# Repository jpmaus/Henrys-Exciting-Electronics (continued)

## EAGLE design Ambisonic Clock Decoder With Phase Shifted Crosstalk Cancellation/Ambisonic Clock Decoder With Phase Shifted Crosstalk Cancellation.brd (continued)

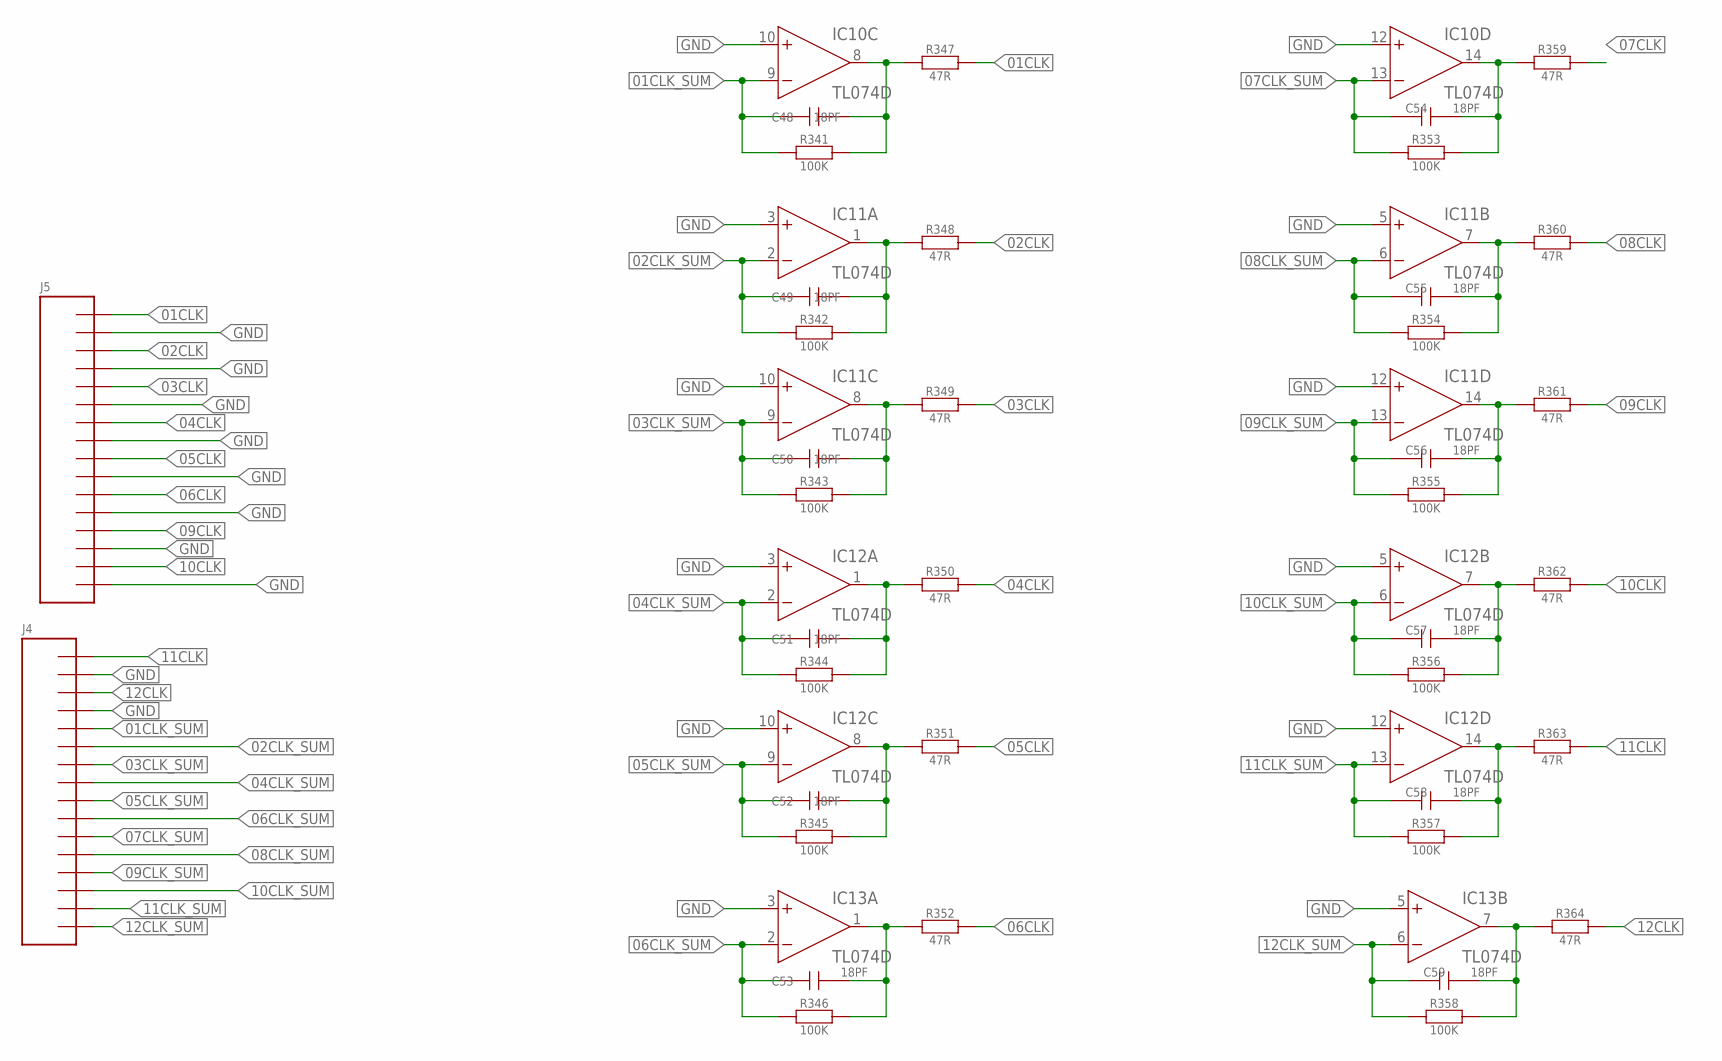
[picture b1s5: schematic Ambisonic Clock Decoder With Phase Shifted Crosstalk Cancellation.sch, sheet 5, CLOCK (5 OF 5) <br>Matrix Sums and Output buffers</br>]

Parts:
C48, C49, C50, C51, C52, C53, C54, C55, C56, C57, C58, C59: 18PF; CT6032
IC10, IC11, IC12, IC13: TL074D; SO14
J4, J5: CON_16; 2X08SMT
R341, R342, R343, R344, R345, R346, R353, R354, R355, R356, R357, R358: 100K; R6332W
R347, R348, R349, R350, R351, R352, R359, R360, R361, R362, R363, R364: 47R; R6332W

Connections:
01CLK: J5.1, R347.2
01CLK_SUM: C48.+ (1), IC10.9 (-IN), J4.5, R341.1
02CLK: J5.3, R348.2
02CLK_SUM: C49.+ (1), IC11.2 (-IN), J4.6, R342.1
03CLK: J5.5, R349.2
03CLK_SUM: C50.+ (1), IC11.9 (-IN), J4.7, R343.1
04CLK: J5.7, R350.2
04CLK_SUM: C51.+ (1), IC12.2 (-IN), J4.8, R344.1
05CLK: J5.9, R351.2
05CLK_SUM: C52.+ (1), IC12.9 (-IN), J4.9, R345.1
06CLK: J5.11, R352.2
06CLK_SUM: C53.+ (1), IC13.2 (-IN), J4.10, R346.1
07CLK: R359.2
07CLK_SUM: C54.+ (1), IC10.13 (-IN), J4.11, R353.1
08CLK: R360.2
08CLK_SUM: C55.+ (1), IC11.6 (-IN), J4.12, R354.1
09CLK: J5.13, R361.2
09CLK_SUM: C56.+ (1), IC11.13 (-IN), J4.13, R355.1
10CLK: J5.15, R362.2
10CLK_SUM: C57.+ (1), IC12.6 (-IN), J4.14, R356.1
11CLK: J4.1, R363.2
11CLK_SUM: C58.+ (1), IC12.13 (-IN), J4.15, R357.1
12CLK: J4.3, R364.2
12CLK_SUM: C59.+ (1), IC13.6 (-IN), J4.16, R358.1
GND: IC10.10 (+IN), IC10.12 (+IN), IC11.3 (+IN), IC11.5 (+IN), IC11.10 (+IN), IC11.12 (+IN), IC12.3 (+IN), IC12.5 (+IN), IC12.10 (+IN), IC12.12 (+IN), IC13.3 (+IN), IC13.5 (+IN), J4.2, J4.4, J5.2, J5.4, J5.6, J5.8, J5.10, J5.12, J5.14, J5.16; also elsewhere on the board
unnamed: C48.- (2), IC10.8 (OUT), R341.2, R347.1
unnamed: C49.- (2), IC11.1 (OUT), R342.2, R348.1
unnamed: C50.- (2), IC11.8 (OUT), R343.2, R349.1
unnamed: C51.- (2), IC12.1 (OUT), R344.2, R350.1
unnamed: C52.- (2), IC12.8 (OUT), R345.2, R351.1
unnamed: C53.- (2), IC13.1 (OUT), R346.2, R352.1
unnamed: C54.- (2), IC10.14 (OUT), R353.2, R359.1
unnamed: C55.- (2), IC11.7 (OUT), R354.2, R360.1
unnamed: C56.- (2), IC11.14 (OUT), R355.2, R361.1
unnamed: C57.- (2), IC12.7 (OUT), R356.2, R362.1
unnamed: C58.- (2), IC12.14 (OUT), R357.2, R363.1
unnamed: C59.- (2), IC13.7 (OUT), R358.2, R364.1
V+: IC10.4 (V+), IC11.4 (V+), IC12.4 (V+), IC13.4 (V+); also elsewhere on the board
V-: IC10.11 (V-), IC11.11 (V-), IC12.11 (V-), IC13.11 (V-); also elsewhere on the board

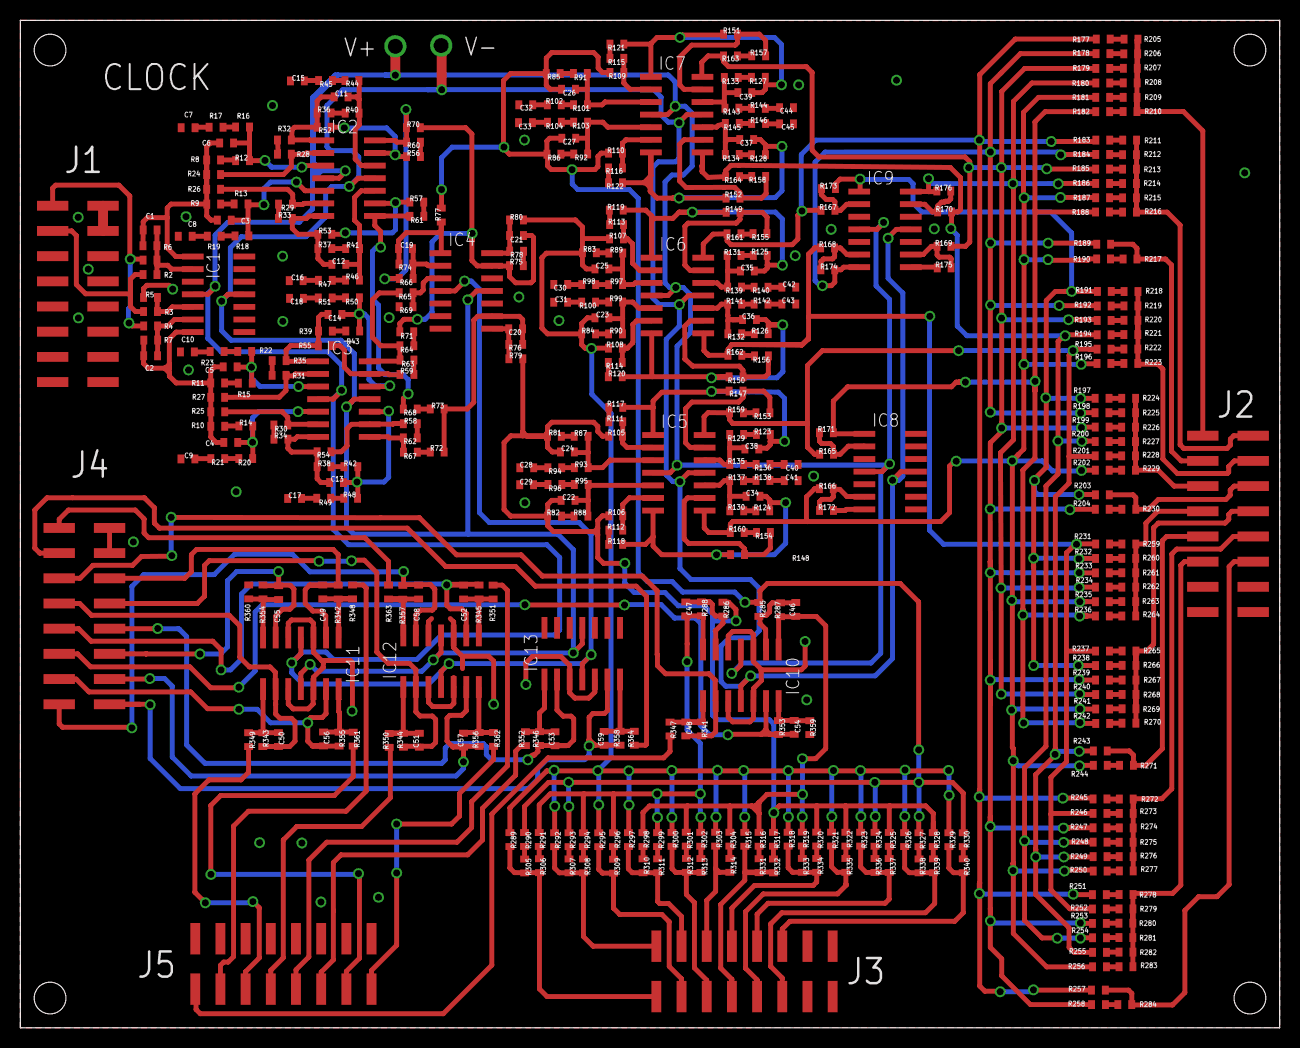
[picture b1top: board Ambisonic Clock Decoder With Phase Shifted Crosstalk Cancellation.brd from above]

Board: 2 copper layers, 127.0 x 101.6 mm, 441 parts (0 on the bottom side), 310 nets.

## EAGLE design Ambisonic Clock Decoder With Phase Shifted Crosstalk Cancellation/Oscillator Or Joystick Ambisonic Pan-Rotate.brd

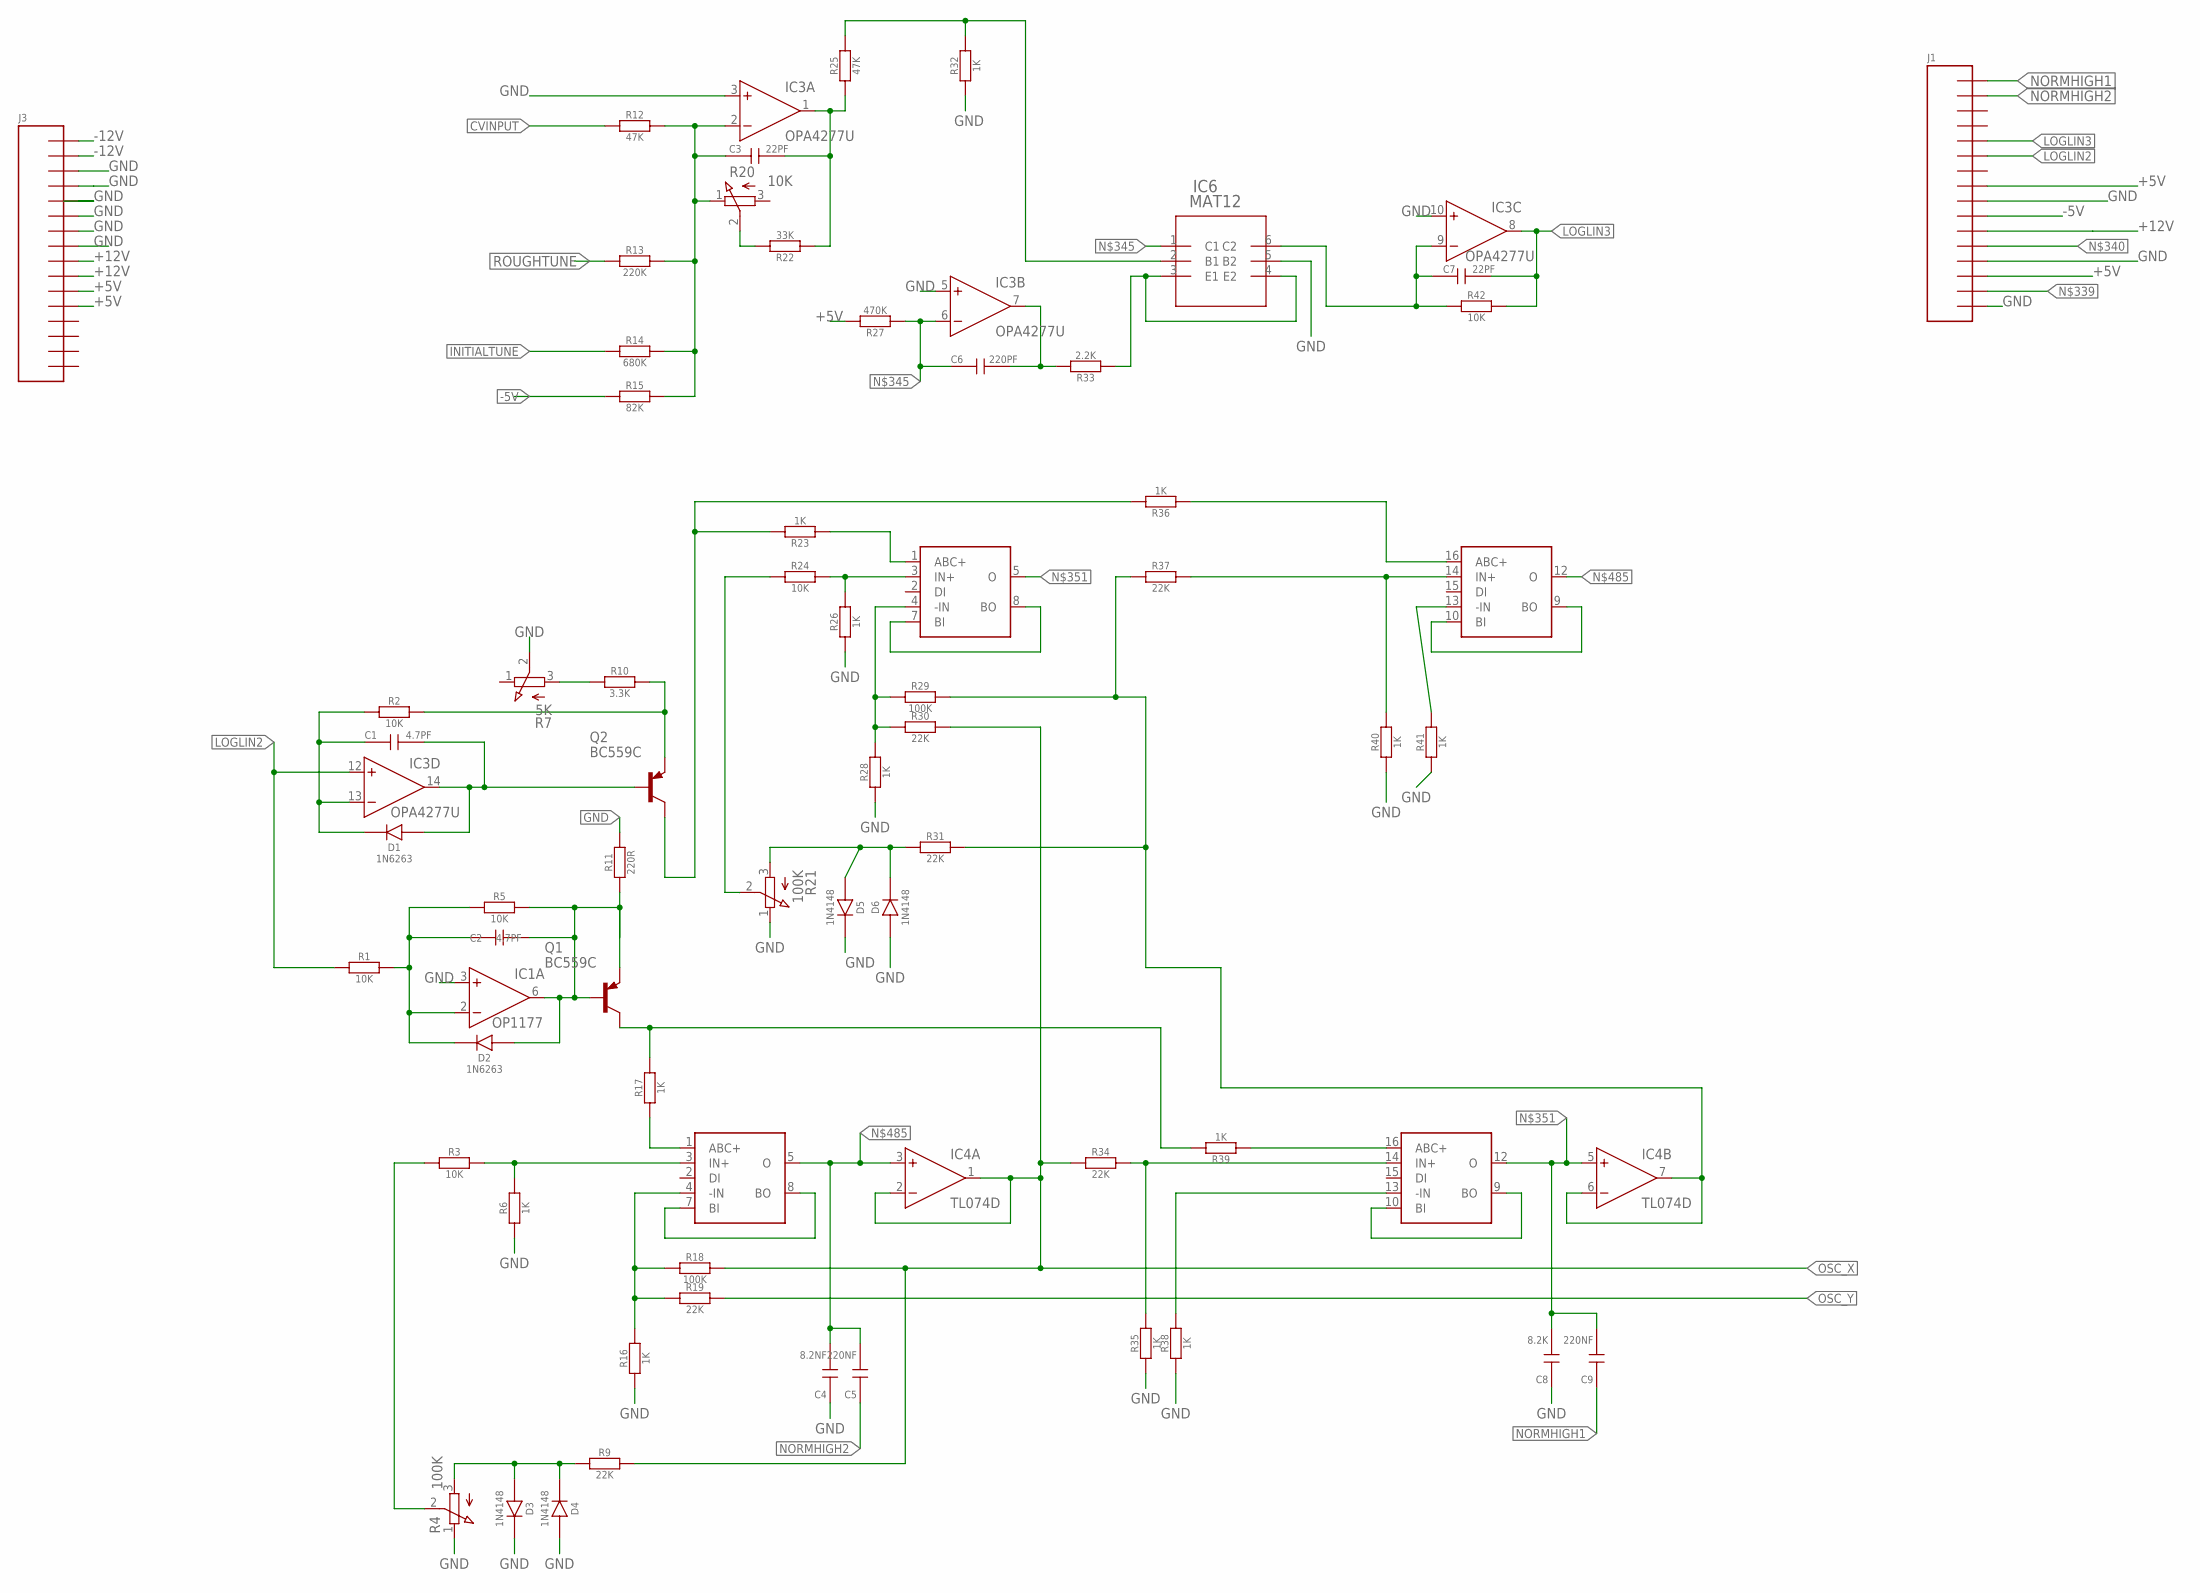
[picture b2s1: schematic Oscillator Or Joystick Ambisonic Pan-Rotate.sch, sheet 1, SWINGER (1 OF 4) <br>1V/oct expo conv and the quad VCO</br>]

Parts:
C1, C2: 4.7PF; CT6032
C3, C7: 22PF; CT6032
C4: 8.2NF; CT6032
C5, C9: 220NF; CT6032
C6: 220PF; CT6032
C8: 8.2K; CT6032
D1, D2: 1N6263; SOD123
D3, D4, D5, D6: 1N4148; SOD123
IC1: OP1177; SO08
IC2, IC5: LM13700; SO16
IC3: OPA4277U; SO14
IC4: TL074D; SO14
IC6: MAT12; H_6
J1, J3: CON_16; 2X08SMT
Q1, Q2: BC559C; TO92
R1, R2, R3, R5, R24, R42: 10K; R6332W
R4, R21: 100K; TRIM
R6, R16, R17, R23, R26, R28, R32, R35, R36, R38, R39, R40, R41: 1K; R6332W
R7: 5K; TRIM
R9, R19, R30, R31, R34, R37: 22K; R6332W
R10: 3.3K; R6332W
R11: 220R; R6332W
R12, R25: 47K; R6332W
R13: 220K; R6332W
R14: 680K; R6332W
R15: 82K; R6332W
R18, R29: 100K; R6332W
R20: 10K; TRIM
R22: 33K; R6332W
R27: 470K; R6332W
R33: 2.2K; R6332W

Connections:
+5V: J1.8, J1.14, J3.11, J3.12, R27.2; also elsewhere on the board
+12V: IC2.11 (V+), IC4.4 (V+), J1.11, J3.9, J3.10; also elsewhere on the board
-5V: J1.10, R15.1; also elsewhere on the board
-12V: IC2.6 (V-), IC4.11 (V-), J3.1, J3.2; also elsewhere on the board
CVINPUT: R12.1
GND: C4.+ (1), C8.+ (1), D3.C, D4.A, D5.C, D6.A, IC1.3 (+IN), IC3.3 (+IN), IC3.5 (+IN), IC3.10 (+IN), IC6.5 (B2), J1.9, J1.13, J1.16, J3.3, J3.4, J3.5, J3.6, J3.7, J3.8, R4.1 (A), R6.1, R7.2 (E), R11.2, R16.1, R21.1 (A), R26.1, R28.1, R32.1, R35.1, R38.1, R40.1, R41.1; also elsewhere on the board
INITIALTUNE: R14.1
LOGLIN2: IC3.12 (+IN), J1.6, R1.1
LOGLIN3: C7.- (2), IC3.8 (OUT), J1.5, R42.2
unnamed: C3.+ (1), IC3.2 (-IN), R12.2, R13.2, R14.2, R15.2, R20.1 (A)
unnamed: C3.- (2), IC3.1 (OUT), R22.1, R25.1
unnamed: IC6.2 (B1), R25.2, R32.2
unnamed: C6.- (2), IC3.7 (OUT), R33.2
unnamed: IC6.3 (E1), IC6.4 (E2), R33.1
unnamed: C7.+ (1), IC3.9 (-IN), IC6.6 (C2), R42.1
unnamed: R20.2 (E), R22.2
unnamed: R7.3 (S), R10.1
unnamed: C6.+ (1), IC3.6 (-IN), IC6.1 (C1), R27.1
unnamed: R3.1, R4.2 (E)
unnamed: R21.2 (E), R24.1
unnamed: C8.- (2), C9.- (2), IC2.12 (O), IC4.5 (+IN), IC5.5 (O)
unnamed: C1.+ (1), D1.C, IC3.13 (-IN), R2.1
unnamed: C1.- (2), D1.A, IC3.14 (OUT), Q2.B
unnamed: C2.+ (1), D2.C, IC1.2 (-IN), R1.2, R5.1
unnamed: Q2.E, R2.2, R10.2
unnamed: C2.- (2), D2.A, IC1.6 (OUT), Q1.B, Q1.E, R5.2, R11.1
unnamed: Q2.C, R23.2, R36.2
unnamed: IC2.16 (ABC+), R39.1
unnamed: D3.A, D4.C, R4.3 (S), R9.1
unnamed: IC2.3 (IN+), R3.2, R6.2
unnamed: IC2.1 (ABC+), R17.1
unnamed: IC2.4 (-IN), R16.2, R18.1, R19.1
unnamed: C4.- (2), C5.- (2), IC2.5 (O), IC4.3 (+IN), IC5.12 (O)
unnamed: Q1.C, R17.2, R39.2
unnamed: IC2.7 (BI), IC2.8 (BO)
unnamed: IC2.9 (BO), IC2.10 (BI)
unnamed: IC2.14 (IN+), R34.2, R35.2
unnamed: IC2.13 (-IN), R38.2
unnamed: IC5.13 (-IN), R41.2
unnamed: IC5.3 (IN+), R24.2, R26.2
unnamed: IC5.4 (-IN), R28.2, R29.1, R30.1
unnamed: IC4.6 (-IN), IC4.7 (OUT), R29.2, R31.2, R37.1
unnamed: IC5.9 (BO), IC5.10 (BI)
unnamed: IC5.1 (ABC+), R23.1
unnamed: IC5.16 (ABC+), R36.1
unnamed: IC5.7 (BI), IC5.8 (BO)
unnamed: IC5.14 (IN+), R37.2, R40.2
unnamed: D5.A, D6.C, R21.3 (S), R31.1
NORMHIGH1: C9.+ (1), J1.1
NORMHIGH2: C5.+ (1), J1.2
OSC_X: IC4.1 (OUT), IC4.2 (-IN), R9.2, R18.2, R30.2, R34.1; also elsewhere on the board
OSC_Y: R19.2; also elsewhere on the board
ROUGHTUNE: R13.1

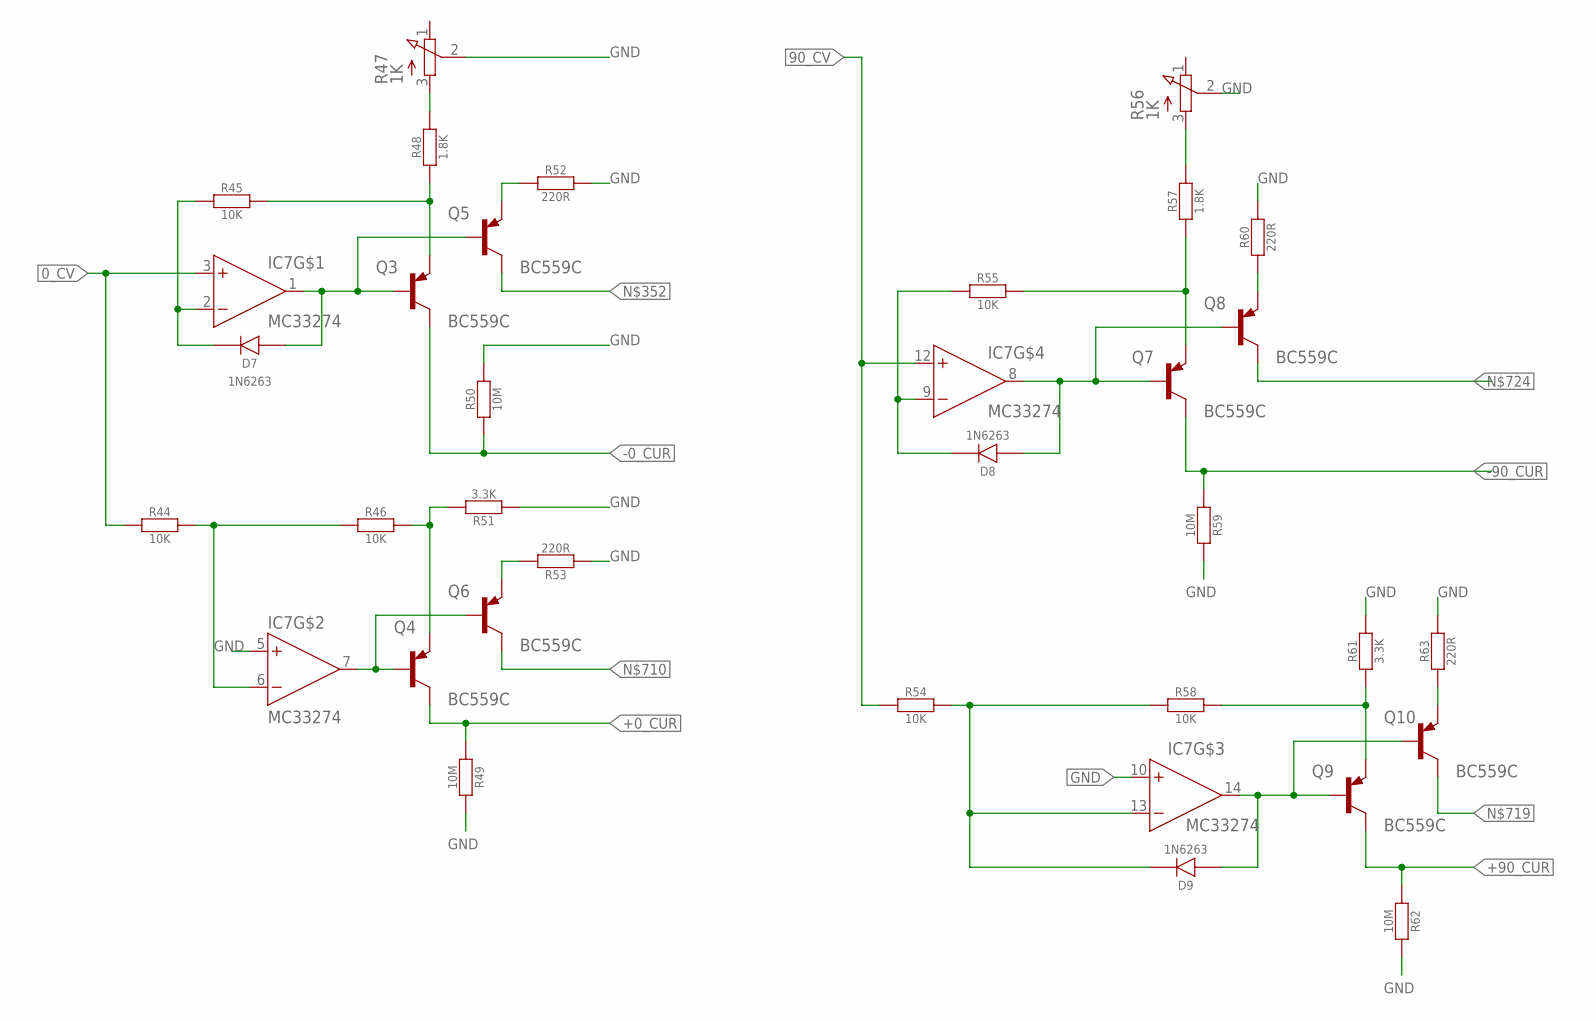
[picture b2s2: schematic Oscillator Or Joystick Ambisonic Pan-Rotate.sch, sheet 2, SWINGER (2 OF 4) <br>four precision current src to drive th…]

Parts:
D7, D8, D9: 1N6263; SOD123
IC7: MC33274; SO14
Q3, Q4, Q5, Q6, Q7, Q8, Q9, Q10: BC559C; TO92
R44, R45, R46, R54, R55, R58: 10K; R6332W
R47, R56: 1K; TRIM
R48, R57: 1.8K; R6332W
R49, R50, R59, R62: 10M; R6332W
R51, R61: 3.3K; R6332W
R52, R53, R60, R63: 220R; R6332W

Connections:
0_CV: IC7.3 (+IN), R44.1; also elsewhere on the board
90_CV: IC7.12 (+IN), R54.1; also elsewhere on the board
+0_CUR: Q4.C, R49.1; also elsewhere on the board
+90_CUR: Q9.C, R62.1; also elsewhere on the board
-0_CUR: Q3.C, R50.1; also elsewhere on the board
-90_CUR: Q7.C, R59.1; also elsewhere on the board
GND: IC7.5 (+IN), IC7.10 (+IN), R47.2 (E), R49.2, R50.2, R51.1, R52.2, R53.1, R56.2 (E), R59.2, R60.2, R61.2, R62.2, R63.2; also elsewhere on the board
unnamed: Q5.E, R52.1
unnamed: R56.3 (S), R57.2
unnamed: IC7.6 (-IN), R44.2, R46.1
unnamed: IC7.7 (OUT), Q4.B, Q6.B
unnamed: Q4.E, R46.2, R51.2
unnamed: Q6.E, R53.2
unnamed: D7.A, IC7.1 (OUT), Q3.B, Q5.B
unnamed: R47.3 (S), R48.2
unnamed: D7.C, IC7.2 (-IN), R45.1
unnamed: Q3.E, R45.2, R48.1
unnamed: D9.C, IC7.13 (-IN), R54.2, R58.1
unnamed: D9.A, IC7.14 (OUT), Q9.B, Q10.B
unnamed: Q9.E, R58.2, R61.1
unnamed: Q10.E, R63.1
unnamed: D8.C, IC7.9 (-IN), R55.1
unnamed: D8.A, IC7.8 (OUT), Q7.B, Q8.B
unnamed: Q7.E, R55.2, R57.1
unnamed: Q8.E, R60.1

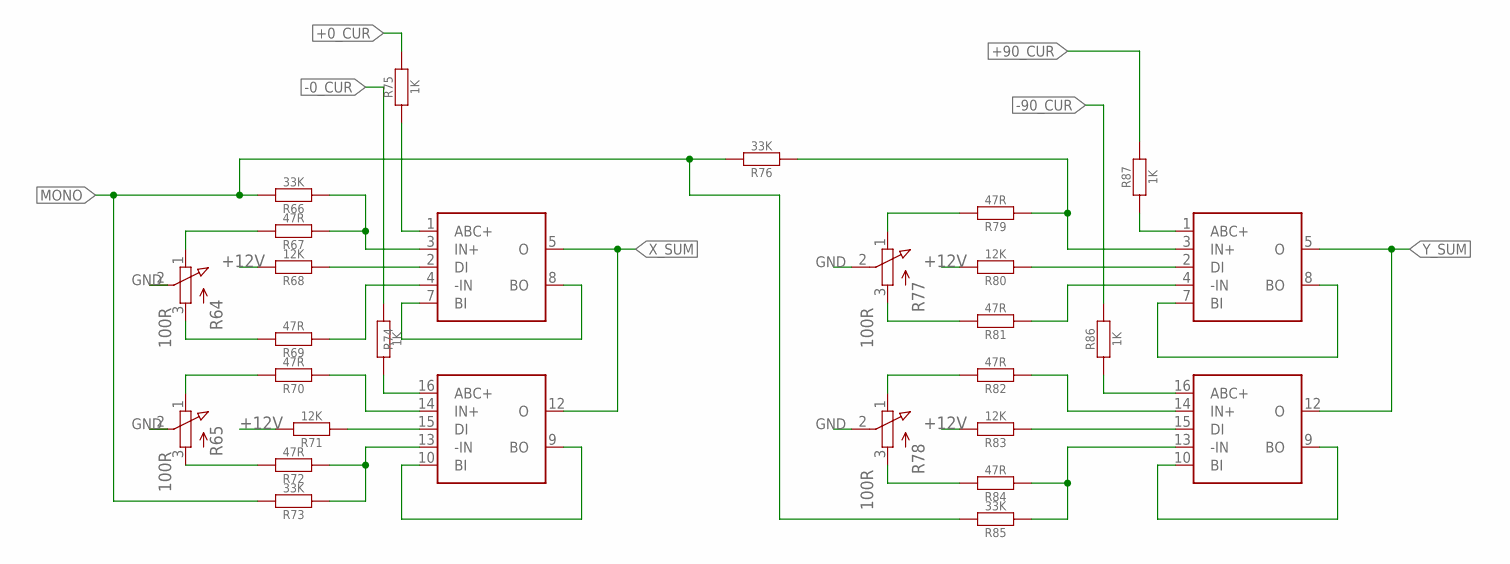
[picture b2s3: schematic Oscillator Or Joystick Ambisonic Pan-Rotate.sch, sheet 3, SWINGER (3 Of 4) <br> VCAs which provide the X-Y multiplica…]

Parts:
IC8, IC9: LM13700; SO16
R64, R65, R77, R78: 100R; TRIM
R66, R73, R76, R85: 33K; R6332W
R67, R69, R70, R72, R79, R81, R82, R84: 47R; R6332W
R68, R71, R80, R83: 12K; R6332W
R74, R75, R86, R87: 1K; R6332W

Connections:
+0_CUR: R75.2; also elsewhere on the board
+12V: R68.2, R71.2, R80.2, R83.2; also elsewhere on the board
+90_CUR: R87.2; also elsewhere on the board
-0_CUR: R74.2; also elsewhere on the board
-90_CUR: R86.2; also elsewhere on the board
GND: R64.2 (E), R65.2 (E), R77.2 (E), R78.2 (E); also elsewhere on the board
MONO: R66.2, R73.2, R76.2, R85.2; also elsewhere on the board
unnamed: IC8.1 (ABC+), R75.1
unnamed: IC8.16 (ABC+), R74.1
unnamed: IC8.3 (IN+), R66.1, R67.1
unnamed: IC8.2 (DI), R68.1
unnamed: IC8.4 (-IN), R69.1
unnamed: IC8.7 (BI), IC8.8 (BO)
unnamed: IC8.9 (BO), IC8.10 (BI)
unnamed: IC8.14 (IN+), R70.1
unnamed: IC8.15 (DI), R71.1
unnamed: IC8.13 (-IN), R72.1, R73.1
unnamed: R65.3 (S), R72.2
unnamed: R65.1 (A), R70.2
unnamed: R64.3 (S), R69.2
unnamed: R64.1 (A), R67.2
unnamed: R77.3 (S), R81.2
unnamed: R77.1 (A), R79.2
unnamed: R78.3 (S), R84.2
unnamed: R78.1 (A), R82.2
unnamed: IC9.14 (IN+), R82.1
unnamed: IC9.13 (-IN), R84.1, R85.1
unnamed: IC9.15 (DI), R83.1
unnamed: IC9.16 (ABC+), R86.1
unnamed: IC9.4 (-IN), R81.1
unnamed: IC9.3 (IN+), R76.1, R79.1
unnamed: IC9.2 (DI), R80.1
unnamed: IC9.7 (BI), IC9.8 (BO)
unnamed: IC9.9 (BO), IC9.10 (BI)
unnamed: IC9.1 (ABC+), R87.1
X_SUM: IC8.5 (O), IC8.12 (O); also elsewhere on the board
Y_SUM: IC9.5 (O), IC9.12 (O); also elsewhere on the board

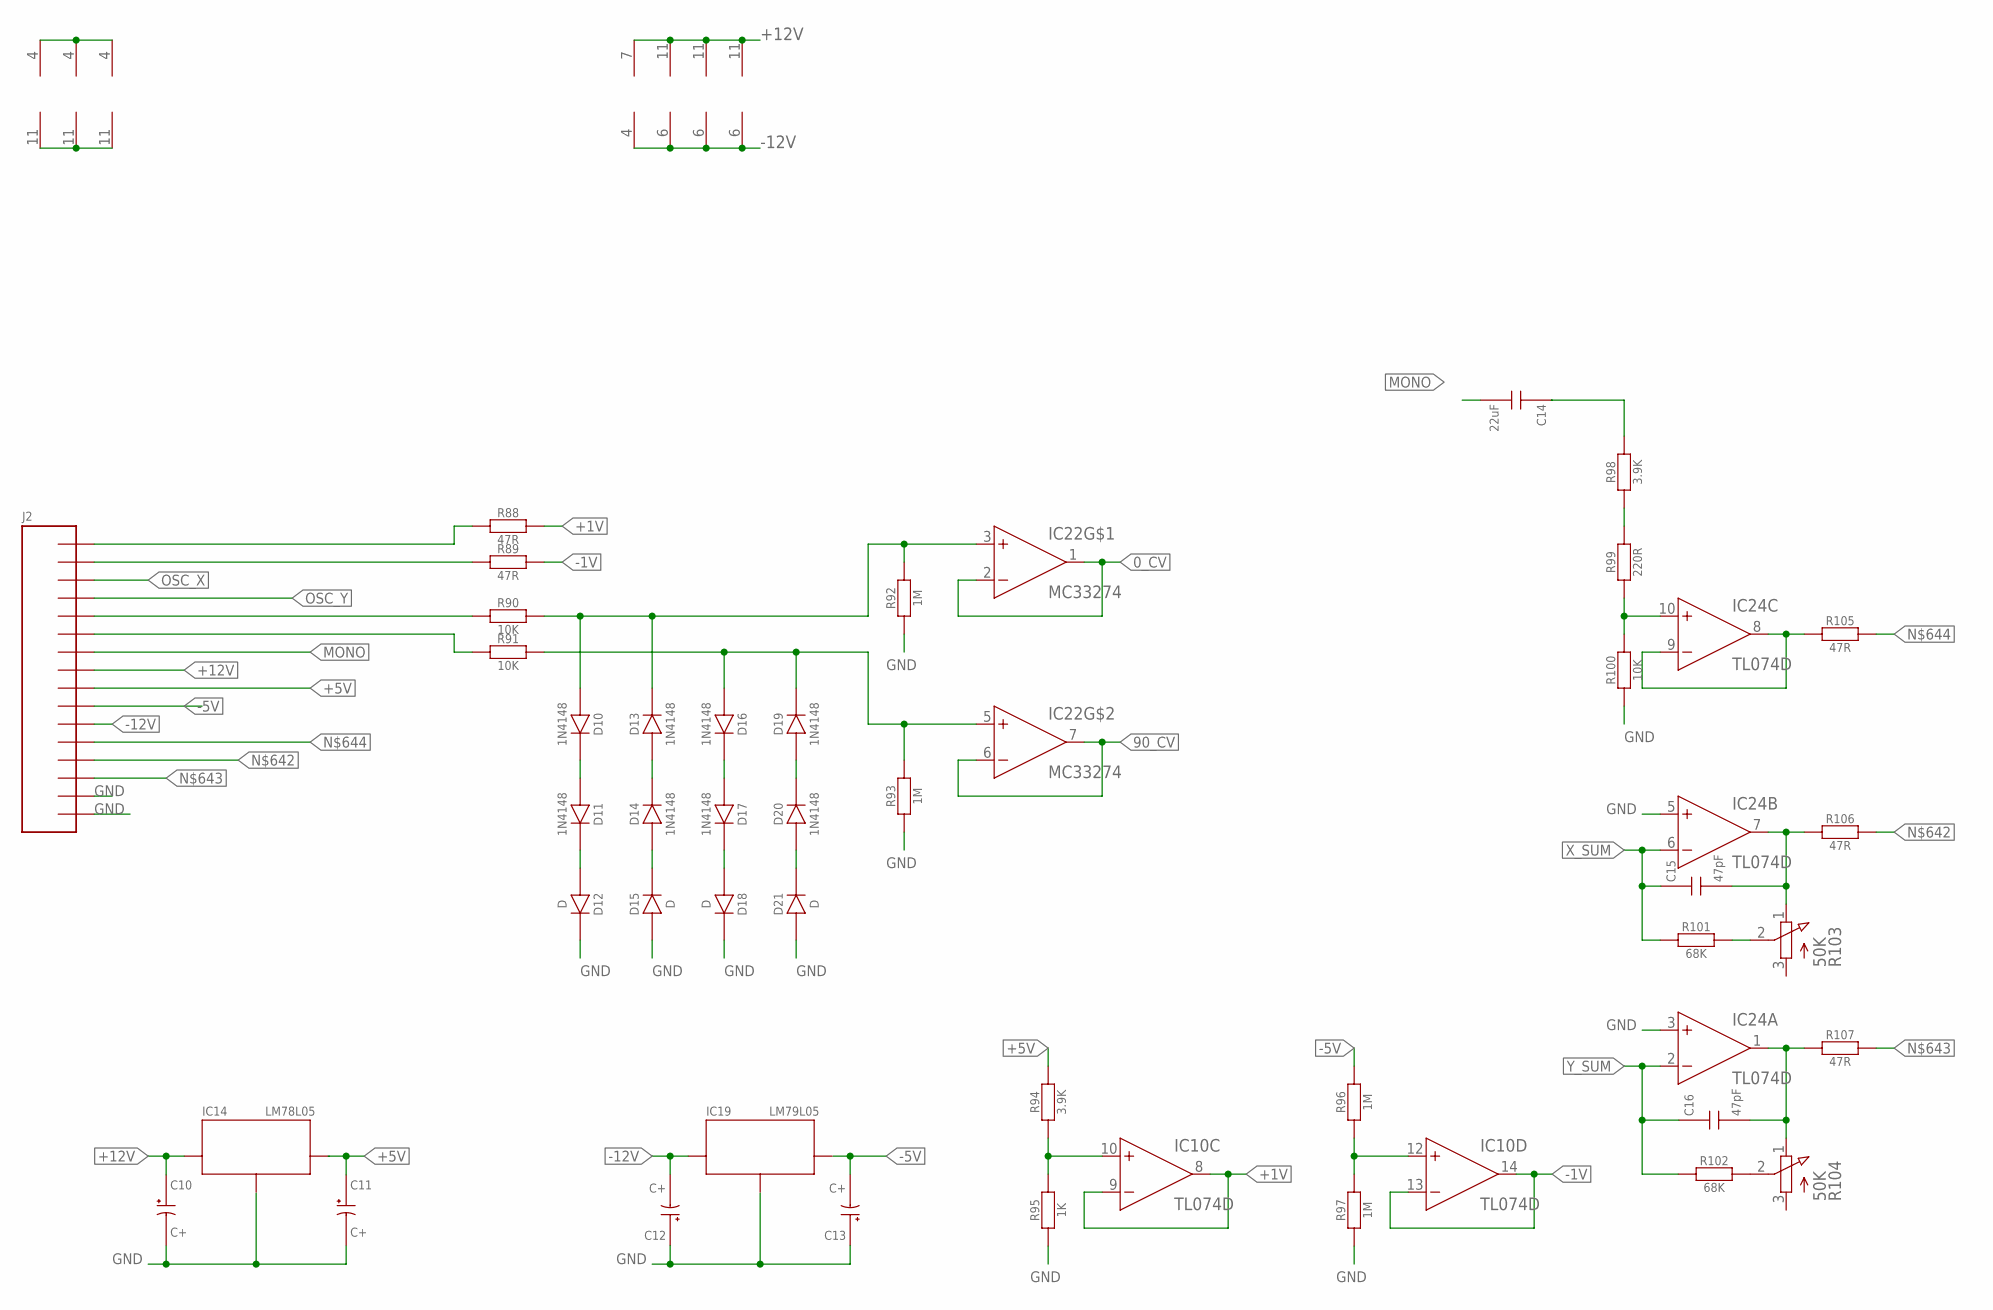
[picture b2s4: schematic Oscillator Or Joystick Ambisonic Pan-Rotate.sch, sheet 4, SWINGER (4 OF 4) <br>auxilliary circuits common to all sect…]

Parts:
C10, C11, C12, C13: C+; PANASONIC_E
C14: 22uF; CT6032
C15, C16: 47pF; CT6032
D10, D11, D13, D14, D16, D17, D19, D20: 1N4148; SOD123
D12, D15, D18, D21: D; SOD123
IC1: OP1177; SO08
IC3: OPA4277U; SO14
IC5, IC8, IC9: LM13700; SO16
IC7, IC22: MC33274; SO14
IC10, IC24: TL074D; SO14
IC14: LM78L05; SO08
IC19: LM79L05; SO08
J2: CON_16; 2X08SMT
R88, R89, R105, R106, R107: 47R; R6332W
R90, R91, R100: 10K; R6332W
R92, R93, R96, R97: 1M; R6332W
R94, R98: 3.9K; R6332W
R95: 1K; R6332W
R99: 220R; R6332W
R101, R102: 68K; R6332W
R103, R104: 50K; TRIM

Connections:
0_CV: IC22.1 (OUT), IC22.2 (-IN); also elsewhere on the board
90_CV: IC22.6 (-IN), IC22.7 (OUT); also elsewhere on the board
+1V: IC10.8 (OUT), IC10.9 (-IN), R88.2
+5V: C11.+ (1), IC14.1 (OUT), J2.9, R94.2; also elsewhere on the board
+12V: C10.+ (1), IC1.7 (V+), IC3.4 (V+), IC5.11 (V+), IC7.4 (V+), IC8.11 (V+), IC9.11 (V+), IC10.4 (V+), IC14.8 (IN), IC22.4 (V+), IC24.4 (V+), J2.8; also elsewhere on the board
-1V: IC10.13 (-IN), IC10.14 (OUT), R89.2
-5V: C13.- (2), IC19.1 (OUT), J2.10, R96.2; also elsewhere on the board
-12V: C12.- (2), IC1.4 (V-), IC3.11 (V-), IC5.6 (V-), IC7.11 (V-), IC8.6 (V-), IC9.6 (V-), IC10.11 (V-), IC19.8 (IN), IC22.11 (V-), IC24.11 (V-), J2.11; also elsewhere on the board
GND: C10.- (2), C11.- (2), C12.+ (1), C13.+ (1), D12.C, D15.A, D18.C, D21.A, IC14.2 (GND), IC14.3 (GND), IC14.6 (GND), IC14.7 (GND), IC19.2 (GND), IC19.3 (GND), IC19.6 (GND), IC19.7 (GND), IC24.3 (+IN), IC24.5 (+IN), J2.15, J2.16, R92.1, R93.1, R95.1, R97.1, R100.1; also elsewhere on the board
MONO: C14.- (2), J2.7; also elsewhere on the board
unnamed: C14.+ (1), R98.2
unnamed: R98.1, R99.2
unnamed: C15.- (2), IC24.7 (OUT), R103.1 (A), R106.1
unnamed: IC10.10 (+IN), R94.1, R95.2
unnamed: J2.1, R88.1
unnamed: IC10.12 (+IN), R96.1, R97.2
unnamed: J2.2, R89.1
unnamed: J2.5, R90.1
unnamed: J2.6, R91.1
unnamed: IC24.10 (+IN), R99.1, R100.2
unnamed: IC24.8 (OUT), IC24.9 (-IN), R105.1
unnamed: R101.2, R103.2 (E)
unnamed: J2.13, R106.2
unnamed: J2.14, R107.2
unnamed: J2.12, R105.2
unnamed: C16.- (2), IC24.1 (OUT), R104.1 (A), R107.1
unnamed: D10.C, D11.A
unnamed: R102.2, R104.2 (E)
unnamed: D11.C, D12.A
unnamed: D13.A, D14.C
unnamed: D14.A, D15.C
unnamed: D17.C, D18.A
unnamed: D16.C, D17.A
unnamed: D20.A, D21.C
unnamed: D19.A, D20.C
unnamed: D10.A, D13.C, IC22.3 (+IN), R90.2, R92.2
unnamed: D16.A, D19.C, IC22.5 (+IN), R91.2, R93.2
OSC_X: J2.3; also elsewhere on the board
OSC_Y: J2.4; also elsewhere on the board
X_SUM: C15.+ (1), IC24.6 (-IN), R101.1; also elsewhere on the board
Y_SUM: C16.+ (1), IC24.2 (-IN), R102.1; also elsewhere on the board

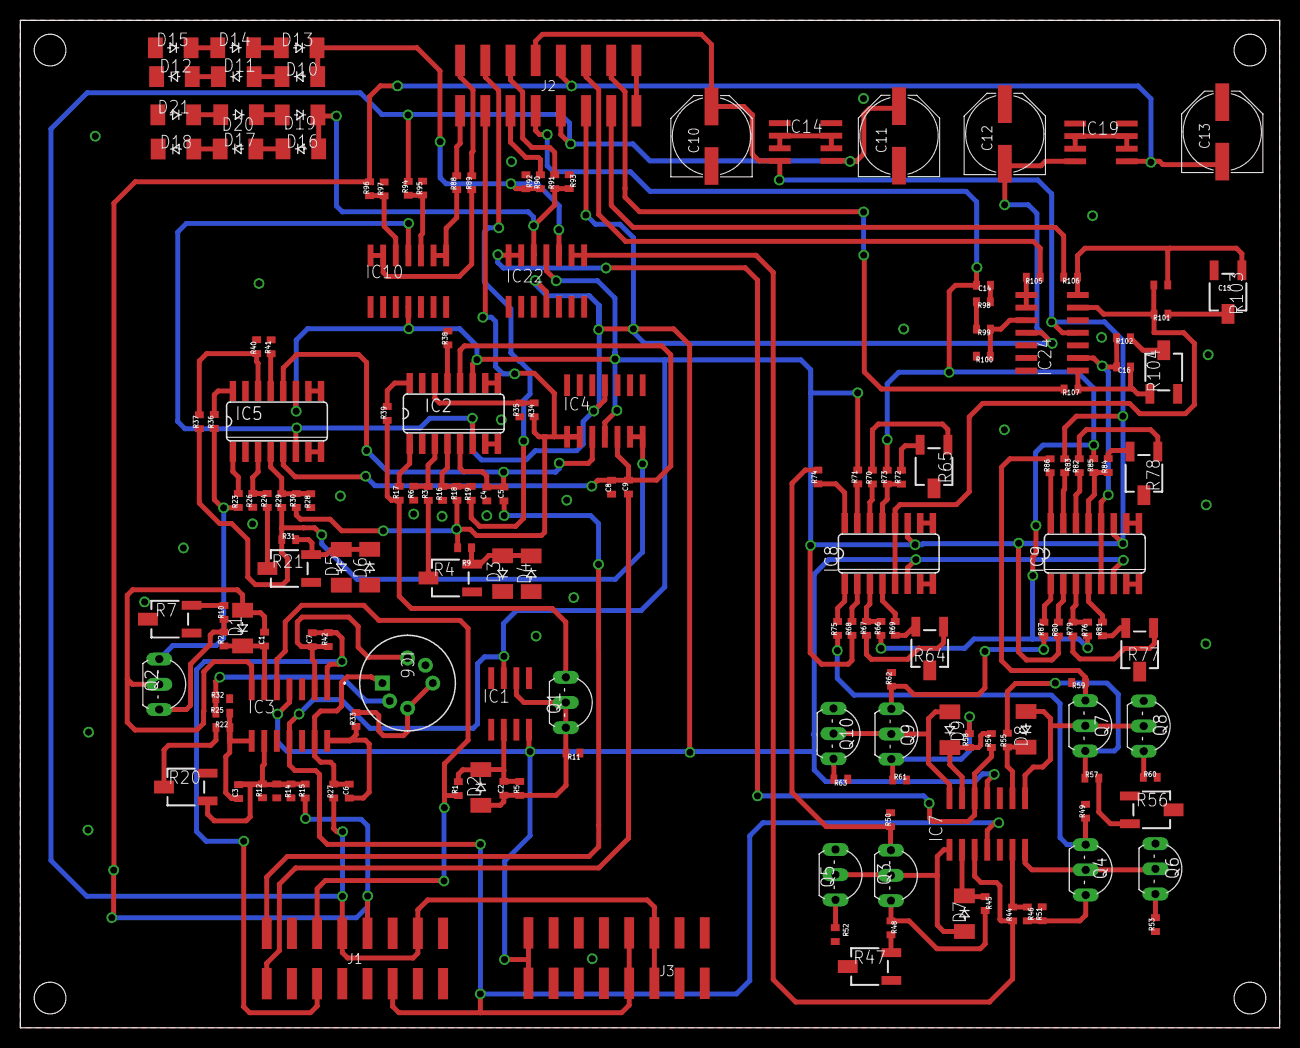
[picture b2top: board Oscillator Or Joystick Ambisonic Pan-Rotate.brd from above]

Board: 2 copper layers, 127.0 x 101.6 mm, 169 parts (0 on the bottom side), 134 nets.

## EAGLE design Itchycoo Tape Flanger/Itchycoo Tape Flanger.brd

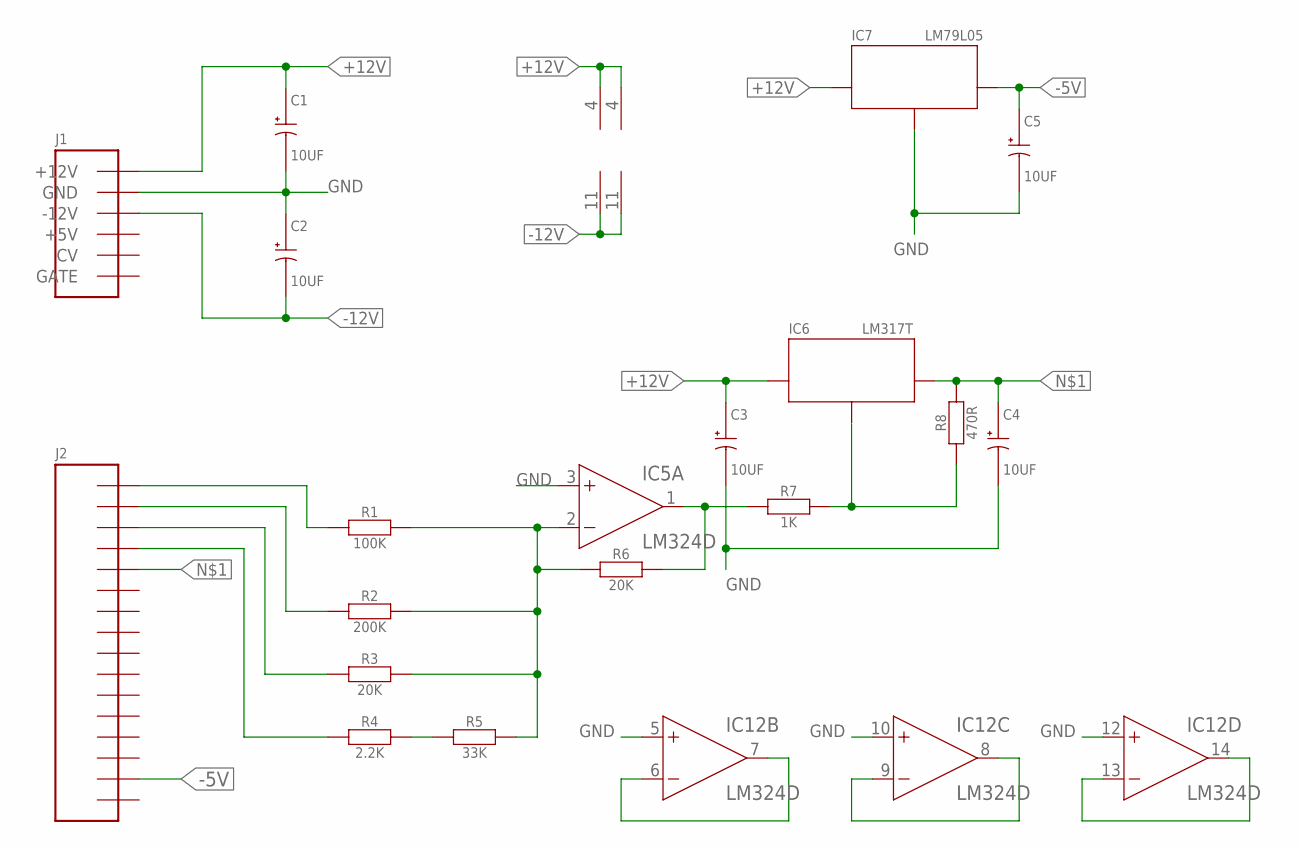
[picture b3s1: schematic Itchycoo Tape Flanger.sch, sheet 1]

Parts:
C1, C2, C3, C4, C5: 10UF; PANASONIC_E
IC5, IC12: LM324D; SO14
IC6: LM317T; SOIC8
IC7: LM79L05; SOIC8
J1: EURO; 2X08SMT
J2: CON_16; 2X08SMT
R1: 100K; R6332W
R2: 200K; R6332W
R3, R6: 20K; R6332W
R4: 2.2K; R6332W
R5: 33K; R6332W
R7: 1K; R6332W
R8: 470R; R6332W

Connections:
+12V: C1.+ (1), C3.+ (1), IC5.4 (V+), IC6.8 (IN), IC7.8 (IN), IC12.4 (V+), J1.9 (+12V), J1.10 (+12V); also elsewhere on the board
-5V: C5.+ (1), IC7.1 (OUT), J2.15
-12V: C2.- (2), IC5.11 (V-), IC12.11 (V-), J1.1 (-12V), J1.2 (-12V); also elsewhere on the board
GND: C1.- (2), C2.+ (1), C3.- (2), C4.- (2), C5.- (2), IC5.3 (+IN), IC7.2 (GND), IC7.3 (GND), IC7.6 (GND), IC7.7 (GND), IC12.5 (+IN), IC12.10 (+IN), IC12.12 (+IN), J1.3 (GND), J1.4 (GND), J1.5 (GND), J1.6 (GND), J1.7 (GND), J1.8 (GND); also elsewhere on the board
unnamed: C4.+ (1), IC6.1 (OUT), J2.5, R8.2
unnamed: J2.4, R4.1
unnamed: J2.3, R3.1
unnamed: R4.2, R5.1
unnamed: IC5.2 (-IN), R1.2, R2.2, R3.2, R5.2, R6.1
unnamed: IC5.1 (OUT), R6.2, R7.1
unnamed: IC6.2 (GND), IC6.3 (GND), IC6.6 (GND), IC6.7 (GND), R7.2, R8.1
unnamed: IC12.8 (OUT), IC12.9 (-IN)
unnamed: J2.2, R2.1
unnamed: IC12.6 (-IN), IC12.7 (OUT)
unnamed: IC12.13 (-IN), IC12.14 (OUT)
unnamed: J2.1, R1.1
